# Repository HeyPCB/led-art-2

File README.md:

# HeyPCB LED Art 2

More shaped LED boards inspired by films: a light bulb for Edison's thousand failures, a starfighter, a submarine, a snowman, an atom, a trophy for the underdog, each in its own colour. KiCad 10, JLCPCB-ready, CERN-OHL-S-2.0.

<p align="center">                                                 </p>

Every board is its own silhouette and solder-mask colour, with addressable RGB LEDs (XL-2020RGBC-2812B, WS2812B-2020 class) following its outline, a CH32V003 RISC-V controller running at 5 V (so it drives the LEDs directly), a MODE button, a 1-wire SWIO programming header, a 3-pin OUT header that chains the light onto the next board, and USB-C power on a tab at the bottom. 4 layers.

| Board | Idea | Mask | Size | DRC errors / unconnected / parity |
|---|---|---|---|---|
| [Angler](boards/angler/) | a light in the deep | Black | 91.3 x 55.39 mm | 0 / 0 / 0 |
| [Atomic](boards/atom-age/) | 1950s sci-fi, three orbits | Blue | 88.01 x 84.85 mm | 0 / 0 / 0 |
| [Gravity](boards/big-apple/) | fell on the right head | Red | 82.77 x 69.86 mm | 0 / 0 / 0 |
| [Bones](boards/bone-skull/) | dead men tell no tales | White | 70 x 77.41 mm | 0 / 0 / 0 |
| [Eureka](boards/bright-idea/) | 1000 ways that did not work | Yellow | 59.97 x 88.98 mm | 0 / 0 / 0 |
| [Champion](boards/champion/) | the underdog takes the cup | Yellow | 83.19 x 91.81 mm | 0 / 0 / 0 |
| [Clock](boards/clock-face/) | 88 mph by midnight | Black | 84.01 x 91.01 mm | 0 / 0 / 0 |
| [Clockwork](boards/clockwork/) | the inventor's workshop | Yellow | 76.01 x 83.01 mm | 0 / 0 / 0 |
| [Compass](boards/compass-rose/) | a map to buried treasure | Blue | 92.01 x 99.01 mm | 0 / 0 / 0 |
| [Cub](boards/cub-paw/) | small paws, big pride | Red | 74 x 79 mm | 0 / 0 / 0 |
| [Cyber Cat](boards/cyber-cat/) | a cat from the neon future | Blue | 74 x 99.01 mm | 0 / 0 / 0 |
| [Dial](boards/decagon-dial/) | tuned to a lost frequency | White | 76.1 x 87.01 mm | 0 / 0 / 0 |
| [High Noon](boards/desert-cactus/) | a spaghetti western standoff | Green | 76.01 x 109.01 mm | 0 / 0 / 0 |
| [Flash](boards/flash-bolt/) | struck by lightning, got fast | Purple | 57.02 x 106.99 mm | 0 / 0 / 0 |
| [Frosty](boards/frosty/) | built from a snow day | White | 52.01 x 93.33 mm | 0 / 0 / 0 |
| [Fruit Bat](boards/fruit-bat/) | out of the cave at dusk | Purple | 112.01 x 74.22 mm | 0 / 0 / 0 |
| [Giant](boards/gas-giant/) | a ringed world far out | Yellow | 113.53 x 75 mm | 0 / 0 / 0 |
| [Big Heart](boards/giant-heart/) | the heart the tin man wanted | White | 94.13 x 92.06 mm | 0 / 0 / 0 |
| [Ice Gem](boards/ice-gem/) | frozen in an ice palace | Blue | 70.01 x 81.01 mm | 0 / 0 / 0 |
| [Jack](boards/jack-lantern/) | carved for a horror double bill | Yellow | 82.81 x 73.61 mm | 0 / 0 / 0 |
| [Jingle](boards/jingle-bell/) | every time a bell rings | Green | 72.9 x 77.53 mm | 0 / 0 / 0 |
| [Sky High](boards/jumbo-cloud/) | a house lifted by balloons | Blue | 94.1 x 63.07 mm | 0 / 0 / 0 |
| [King](boards/kings-crown/) | lost the throne, won it back | Black | 100.01 x 68.92 mm | 0 / 0 / 0 |
| [Cabin](boards/log-cabin/) | a cabin in the woods | Red | 84.01 x 95.21 mm | 0 / 0 / 0 |
| [Love Bug](boards/love-bug/) | a small heart for a rom-com | Red | 60.25 x 61.45 mm | 0 / 0 / 0 |
| [Maple](boards/maple-leaf/) | falling in an autumn scene | Red | 74.15 x 103.99 mm | 0 / 0 / 0 |
| [Mech](boards/mech/) | rebuilt from scrap | Black | 92.01 x 90.01 mm | 0 / 0 / 0 |
| [Mega Gear](boards/mega-gear/) | twenty teeth, one mechanism | White | 92.01 x 99.01 mm | 0 / 0 / 0 |
| [Melody](boards/melody/) | the song from the musical | Black | 55.57 x 101.55 mm | 0 / 0 / 0 |
| [Moth](boards/moth/) | drawn to the light | White | 90.39 x 70.25 mm | 0 / 0 / 0 |
| [Mothership](boards/mothership/) | five tones in the sky | Purple | 112.01 x 64.95 mm | 0 / 0 / 0 |
| [Night Owl](boards/night-owl/) | carrying letters after dark | Purple | 69.99 x 105.41 mm | 0 / 0 / 0 |
| [Shuriken](boards/ninja-star/) | thrown from the shadows | Black | 92.01 x 99.01 mm | 0 / 0 / 0 |
| [Nine](boards/nonagon/) | nine sides, one puzzle | Purple | 78.8 x 84.6 mm | 0 / 0 / 0 |
| [Paladin](boards/paladin/) | dented in a hundred battles | White | 70.01 x 91.01 mm | 0 / 0 / 0 |
| [Phantom](boards/phantom/) | haunting the opera house | Black | 70.01 x 93.75 mm | 0 / 0 / 0 |
| [Raider](boards/pixel-raider/) | insert coin to continue | Purple | 104.89 x 84.29 mm | 0 / 0 / 0 |
| [Portal](boards/portal-ring/) | step through to the other side | Green | 84 x 91.01 mm | 0 / 0 / 0 |
| [Turtle](boards/sea-turtle/) | riding the current | Green | 93.97 x 71.01 mm | 0 / 0 / 0 |
| [Pine](boards/snow-pine/) | a frozen forest | White | 90.01 x 81.01 mm | 0 / 0 / 0 |
| [Astronaut](boards/space-helmet/) | failure is not an option | White | 76 x 87.56 mm | 0 / 0 / 0 |
| [Square One](boards/square-one/) | back to square one, again | Blue | 65.07 x 72.07 mm | 0 / 0 / 0 |
| [Starburst](boards/starburst/) | the opening-night flash | Yellow | 87.51 x 99.01 mm | 0 / 0 / 0 |
| [Starfighter](boards/starfighter/) | delta wing, ready to launch | White | 96.01 x 97.01 mm | 0 / 0 / 0 |
| [Sunset](boards/sunset-disc/) | riding off into it | Red | 92.01 x 99.01 mm | 0 / 0 / 0 |
| [Thunder](boards/thunder-bolt/) | a lightning bolt with a storm inside | Yellow | 61.98 x 115.99 mm | 0 / 0 / 0 |
| [Luna](boards/tiny-moon/) | a small moon, a big story | Purple | 60 x 67.01 mm | 0 / 0 / 0 |
| [Vault](boards/vault-key/) | the key for the heist | Blue | 112.01 x 47.01 mm | 0 / 0 / 0 |
| [Warp](boards/warp-ring/) | a gate to another galaxy | Blue | 92.01 x 99.01 mm | 0 / 0 / 0 |
| [Submarine](boards/yellow-sub/) | all the way under the sea | Yellow | 101.21 x 58.71 mm | 0 / 0 / 0 |

**Not fabricated, assembled or powered.** Every number in a board's README is measured by KiCad 10 on the files in its folder (`report.json`); parts carry LCSC numbers and were in JLCPCB's stock on the date each README gives. Order each board in its stated mask colour. Firmware is not included: these are the boards.

Designed with the HeyPCB method on KiCad 10 by heypcb-kicad's headless pipeline with Freerouting 2.4.1.

## Licence

CERN-OHL-S-2.0, © 2026 heypcb.ai. See [LICENSE](LICENSE).

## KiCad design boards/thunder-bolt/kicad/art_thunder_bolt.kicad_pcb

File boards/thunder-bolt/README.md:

# THUNDER

a lightning bolt with a storm inside

| Layers | Size | Parts | Nets | Connections routed | Vias | ERC errors | DRC errors / unconnected / parity |
|---|---|---|---|---|---|---|---|
| 4 | 61.98 x 115.99 mm | 38 | 24 | 98 -> 0 open | 108 | 0 | 0 / 0 / 0 |

**Not fabricated, assembled or powered.** Every number on this page is measured by KiCad 10 on the files in this folder; the full measurements are in [`report.json`](report.json).

| | |
|---|---|
| KiCad project | [`kicad/`](kicad/) |
| Gerbers, BOM, CPL, STEP, schematic PDF | [`fab/`](fab/) |
| Renders | [top](media/top.png), [bottom](media/bottom.png) |

A yellow lightning bolt whose LEDs strike from top to bottom: the scar, the storm and the superhero logo, as one desk badge. Designed with the HeyPCB method on KiCad 10, by heypcb-kicad's headless pipeline with Freerouting 2.4.1, from the brief in `board.json`.

## Specs

- **Shape:** bolt, 61.98 x 115.99 mm, yellow solder mask, 4 layers, 1.6 mm. A 16 mm tab at the bottom carries the USB-C receptacle.
- **Light:** 13 XL-2020RGBC-2812B addressable RGB LEDs (WS2812B-2020 class, 2 x 2 mm) chained around the outline, each with its own 100 nF.
- **Controller:** CH32V003F4P6 RISC-V MCU at 5 V (so its data output meets the LEDs' 5 V logic with no translator), programmed over the 1-wire SWIO header with a WCH-LinkE; MODE button on PC0.
- **Power:** USB-C 5 V (5.1k on CC1 and CC2). 13 LEDs at full white would draw about 0.5 A, so firmware caps brightness to stay inside a 0.5 A USB port (about 14 % average).

## Parts

Every line carries an LCSC part number. Stock is JLCPCB's assembly stock on 2026-10-19.

| Designators | Value | LCSC | MPN | JLCPCB tier | Stock |
|---|---|---|---|---|---|
| C1,C2 | 10uF | C15850 | CL21A106KAYNNNE | Basic | 6,481,857 |
| C3,C4,C5,C6,C7,C8,C9,C10,C11,C12,C13,C14,C15,C16 | 100nF | C1525 | CL05B104KO5NNNC | Basic | 29,476,420 |
| D1,D2,D3,D4,D5,D6,D7,D8,D9,D10,D11,D12,D13 | XL-2020RGBC-2812B | C5349955 | XL-2020RGBC-2812B | Extended | 100,374 |
| J1 | USB-C | C165948 | TYPE-C-31-M-12 | Extended | 357,307 |
| J2 | SWIO | C2937625 | PZ254V-11-03P | Extended | 924,821 |
| J3 | OUT | C2937625 | PZ254V-11-03P | Extended | 924,821 |
| R1,R2 | 5.1k | C25905 | 0402WGF5101TCE | Basic | 5,086,543 |
| R3 | 33 | C23140 | 0603WAF330JT5E | Basic | 4,946,796 |
| R4 | 10k | C25804 | 0603WAF1002T5E | Basic | 39,931,112 |
| SW1 | MODE | C318884 | TS-1187A-B-A-B | Basic | 290,976 |
| U1 | CH32V003F4P6 | C5187096 | CH32V003F4P6 | Extended | 26,142 |

## Ordering

- PCB: upload `fab/art_thunder_bolt_gerbers.zip`, 4 layers, 61.98 x 115.99 mm, 1.6 mm, yellow solder mask with black silkscreen.
- Assembly: `fab/art_thunder_bolt_bom.csv` and `fab/art_thunder_bolt_cpl_jlc.csv`, top side.
- The CPL is fitted to each part's own JLCPCB footprint, pad by pad, and re-checked by laying each footprint where its row says: 37 of 38 rows fitted, worst pin-to-pad offset 0.26 mm.
- Not fitted (no JLCPCB footprint to fit to), rotation from KiCad's: SW1. Check these in JLCPCB's placement preview.

## Notes

- The USB-C receptacle renders as a plain box: KiCad's footprint names a 3D model KiCad does not ship.
- Firmware is not part of this repository: the board is the hardware. Not built or measured.

## How it was made

Designed with the HeyPCB method on KiCad 10, by heypcb-kicad's headless pipeline with Freerouting 2.4.1, from the brief in [`board.json`](board.json).

## Licence

CERN-OHL-S-2.0, © 2026 heypcb.ai. See the collection's LICENSE.

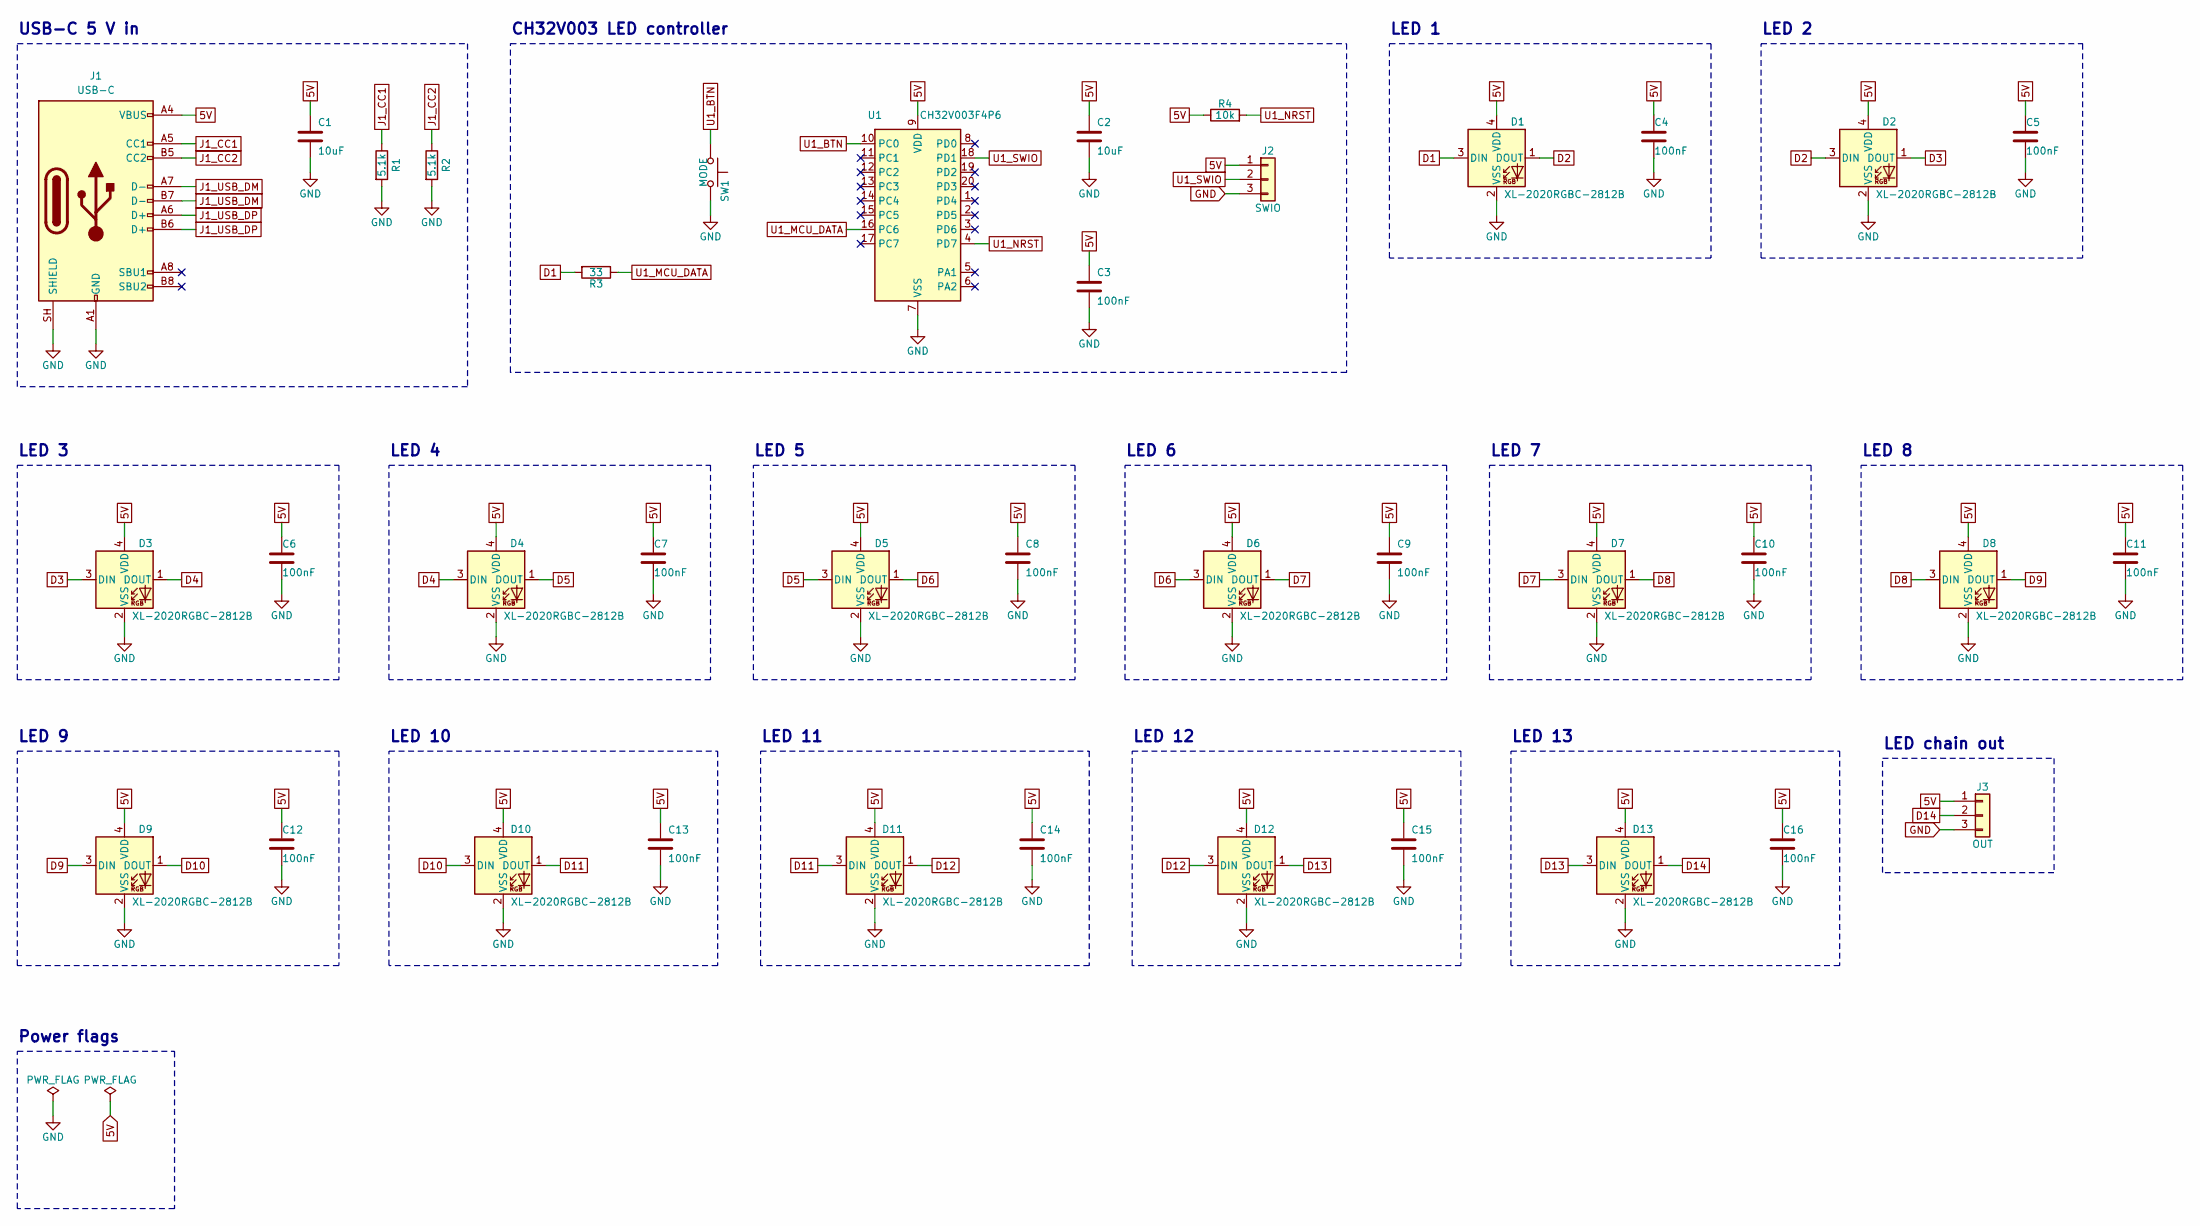
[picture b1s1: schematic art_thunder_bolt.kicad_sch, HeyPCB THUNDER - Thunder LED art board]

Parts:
C1, C2: 10uF; C_0805_2012Metric; MPN CL21A106KAYNNNE; LCSC C15850
C3, C4, C5, C6, C7, C8, C9, C10, C11, C12, C13, C14, C15, C16: 100nF; C_0402_1005Metric; MPN CL05B104KO5NNNC; LCSC C1525
D1, D2, D3, D4, D5, D6, D7, D8, D9, D10, D11, D12, D13: XL-2020RGBC-2812B; LED_WS2812B-2020_PLCC4_2.0x2.0mm; MPN XL-2020RGBC-2812B; LCSC C5349955
J1: USB-C; USB_C_Receptacle_HRO_TYPE-C-31-M-12; MPN TYPE-C-31-M-12; LCSC C165948
J2: SWIO; PinHeader_1x03_P2.54mm_Vertical; MPN PZ254V-11-03P; LCSC C2937625
J3: OUT; PinHeader_1x03_P2.54mm_Vertical; MPN PZ254V-11-03P; LCSC C2937625
R1, R2: 5.1k; R_0402_1005Metric; MPN 0402WGF5101TCE; LCSC C25905
R3: 33; R_0603_1608Metric; MPN 0603WAF330JT5E; LCSC C23140
R4: 10k; R_0603_1608Metric; MPN 0603WAF1002T5E; LCSC C25804
SW1: MODE; SW_Push_1P1T_XKB_TS-1187A; MPN TS-1187A-B-A-B; LCSC C318884
U1: CH32V003F4P6; TSSOP-20_4.4x6.5mm_P0.65mm; MPN CH32V003F4P6; LCSC C5187096

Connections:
5V: C1.1, C2.1, C3.1, C4.1, C5.1, C6.1, C7.1, C8.1, C9.1, C10.1, C11.1, C12.1, C13.1, C14.1, C15.1, C16.1, D1.4 (VDD), D2.4 (VDD), D3.4 (VDD), D4.4 (VDD), D5.4 (VDD), D6.4 (VDD), D7.4 (VDD), D8.4 (VDD), D9.4 (VDD), D10.4 (VDD), D11.4 (VDD), D12.4 (VDD), D13.4 (VDD), J1.A4 (VBUS), J1.A9 (VBUS), J1.B4 (VBUS), J1.B9 (VBUS), J2.1, J3.1, R4.1, U1.9 (VDD)
D1: D1.3 (DIN), R3.2
D2: D1.1 (DOUT), D2.3 (DIN)
D3: D2.1 (DOUT), D3.3 (DIN)
D4: D3.1 (DOUT), D4.3 (DIN)
D5: D4.1 (DOUT), D5.3 (DIN)
D6: D5.1 (DOUT), D6.3 (DIN)
D7: D6.1 (DOUT), D7.3 (DIN)
D8: D7.1 (DOUT), D8.3 (DIN)
D9: D8.1 (DOUT), D9.3 (DIN)
D10: D9.1 (DOUT), D10.3 (DIN)
D11: D10.1 (DOUT), D11.3 (DIN)
D12: D11.1 (DOUT), D12.3 (DIN)
D13: D12.1 (DOUT), D13.3 (DIN)
D14: D13.1 (DOUT), J3.2
GND: C1.2, C2.2, C3.2, C4.2, C5.2, C6.2, C7.2, C8.2, C9.2, C10.2, C11.2, C12.2, C13.2, C14.2, C15.2, C16.2, D1.2 (VSS), D2.2 (VSS), D3.2 (VSS), D4.2 (VSS), D5.2 (VSS), D6.2 (VSS), D7.2 (VSS), D8.2 (VSS), D9.2 (VSS), D10.2 (VSS), D11.2 (VSS), D12.2 (VSS), D13.2 (VSS), J1.A1 (GND), J1.A12 (GND), J1.B1 (GND), J1.B12 (GND), J1.SH (SHIELD), J2.3, J3.3, R1.2, R2.2, SW1.2, U1.7 (VSS)
J1_CC1: J1.A5 (CC1), R1.1
J1_CC2: J1.B5 (CC2), R2.1
J1_USB_DM: J1.A7 (D-), J1.B7 (D-)
J1_USB_DP: J1.A6 (D+), J1.B6 (D+)
U1_BTN: SW1.1, U1.10 (PC0)
U1_MCU_DATA: R3.1, U1.16 (PC6)
U1_NRST: R4.2, U1.4 (PD7)
U1_SWIO: J2.2, U1.18 (PD1)

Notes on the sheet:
USB-C 5 V in
CH32V003 LED controller
LED 1
LED 2
LED 3
LED 4
LED 5
LED 6
LED 7
LED 8
LED 9
LED 10
LED 11
LED 12
LED 13
LED chain out
Power flags

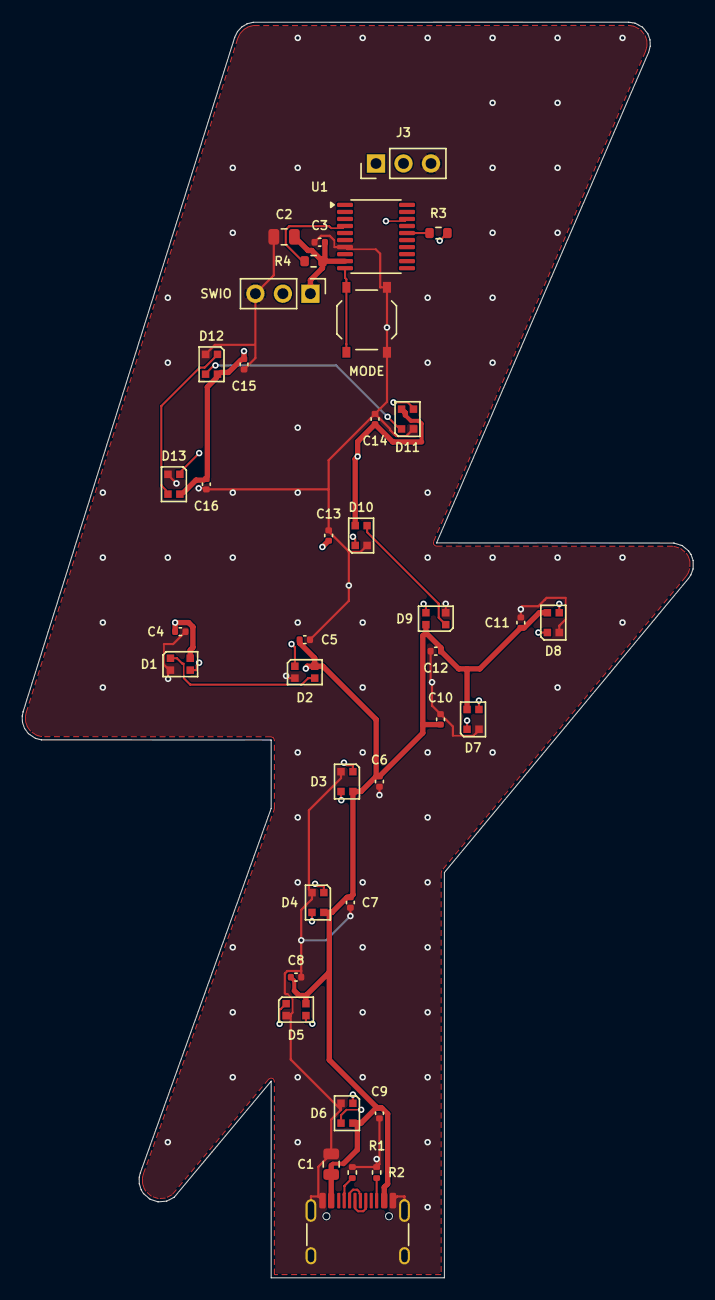
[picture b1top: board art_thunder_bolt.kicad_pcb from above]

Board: 4 copper layers, 62.0 x 116.0 mm, 38 parts (0 on the bottom side), 24 nets.

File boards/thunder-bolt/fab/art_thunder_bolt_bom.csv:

"Reference","Value","Footprint","MPN","LCSC","Qty"
"C1,C2","10uF","Capacitor_SMD:C_0805_2012Metric","CL21A106KAYNNNE","C15850","2"
"C3,C4,C5,C6,C7,C8,C9,C10,C11,C12,C13,C14,C15,C16","100nF","Capacitor_SMD:C_0402_1005Metric","CL05B104KO5NNNC","C1525","14"
"D1,D2,D3,D4,D5,D6,D7,D8,D9,D10,D11,D12,D13","XL-2020RGBC-2812B","LED_SMD:LED_WS2812B-2020_PLCC4_2.0x2.0mm","XL-2020RGBC-2812B","C5349955","13"
"J1","USB-C","Connector_USB:USB_C_Receptacle_HRO_TYPE-C-31-M-12","TYPE-C-31-M-12","C165948","1"
"J2","SWIO","Connector_PinHeader_2.54mm:PinHeader_1x03_P2.54mm_Vertical","PZ254V-11-03P","C2937625","1"
"J3","OUT","Connector_PinHeader_2.54mm:PinHeader_1x03_P2.54mm_Vertical","PZ254V-11-03P","C2937625","1"
"R1,R2","5.1k","Resistor_SMD:R_0402_1005Metric","0402WGF5101TCE","C25905","2"
"R3","33","Resistor_SMD:R_0603_1608Metric","0603WAF330JT5E","C23140","1"
"R4","10k","Resistor_SMD:R_0603_1608Metric","0603WAF1002T5E","C25804","1"
"SW1","MODE","Button_Switch_SMD:SW_Push_1P1T_XKB_TS-1187A","TS-1187A-B-A-B","C318884","1"
"U1","CH32V003F4P6","Package_SO:TSSOP-20_4.4x6.5mm_P0.65mm","CH32V003F4P6","C5187096","1"
